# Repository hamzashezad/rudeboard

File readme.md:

# the rudeboard ™

by rudeyboy (rudeyboy#0420 on discord) and hangry -- me (hangry#9198 on discord)

---

introducing the rudeboard:

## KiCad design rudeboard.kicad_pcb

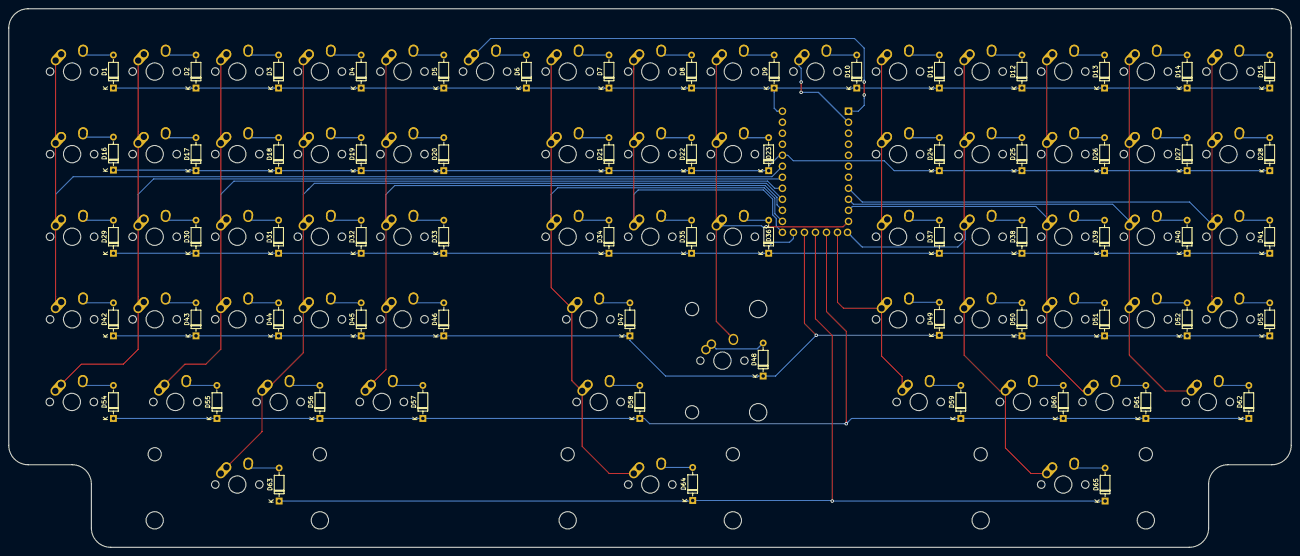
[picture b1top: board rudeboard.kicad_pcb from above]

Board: 2 copper layers, 295.8 x 124.2 mm, 131 parts (1 on the bottom side), 86 nets.

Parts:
D1, D2, D3, D4, D5, D6, D7, D8, D9, D10, D11, D12, D13, D14, D15, D16, D17, D18, D19, D20, D21, D22, D23, D24, D25, D26, D27, D28, D29, D30, D31, D32, D33, D34, D35, D36, D37, D38, D39, D40, D41, D42, D43, D44, D45, D46, D47, D48, D49, D50, D51, D52, D53, D54, D55, D56, D57, D58, D59, D60, D61, D62, D63, D64, D65: D_Small; D_DO-35_SOD27_P7.62mm_Horizontal
MX1, MX2, MX3, MX4, MX5, MX6, MX7, MX8, MX9, MX10, MX11, MX12, MX13, MX14, MX15, MX16, MX17, MX18, MX19, MX20, MX21, MX22, MX23, MX24, MX25, MX26, MX27, MX28, MX29, MX30, MX31, MX32, MX33, MX34, MX35, MX36, MX37, MX38, MX39, MX40, MX41, MX42, MX43, MX44, MX45, MX46, MX49, MX50, MX51, MX52, MX53, MX54, MX56, MX60, MX61: MX-NoLED; MX-1U-NoLED
MX47, MX55, MX57, MX59, MX62: MX-NoLED; MX-1.5U-NoLED
MX48: MX-NoLED; SW_Cherry_MX_ISOEnter_PCB
MX58: MX-NoLED; MX-1.75U-NoLED
MX63, MX64, MX65: MX-NoLED; MX-3U-NoLED
U1: Elite-C

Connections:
/col0: MX1.1, MX16.1, MX29.1, MX42.1, U1.19
/col1: MX2.1, MX17.1, MX30.1, MX43.1, MX54.1, U1.18
/col2: MX3.1, MX18.1, MX31.1, MX44.1, MX55.1, U1.17
/col3: MX4.1, MX19.1, MX32.1, MX45.1, MX56.1, MX63.1, U1.16
/col4: MX5.1, MX20.1, MX33.1, MX46.1, MX57.1, U1.15
/col5: MX6.1, U1.1
/col6: MX7.1, MX21.1, MX34.1, MX47.1, MX58.1, MX64.1, U1.14
/col7: MX8.1, MX22.1, MX35.1, U1.13
/col8: MX9.1, MX23.1, MX36.1, MX48.1, U1.11
/col9: MX10.1, U1.2
/col10: MX11.1, MX24.1, MX37.1, MX49.1, MX59.1, U1.25
/col11: MX12.1, MX25.1, MX38.1, MX50.1, MX60.1, MX65.1, U1.12
/col12: MX13.1, MX26.1, MX39.1, MX51.1, MX61.1, U1.10
/col13: MX14.1, MX27.1, MX40.1, MX52.1, MX62.1, U1.9
/col14: MX15.1, MX28.1, MX41.1, MX53.1, U1.8
/row0: D1.1, D2.1, D3.1, D4.1, D5.1, D6.1, D7.1, D8.1, D9.1, D10.1, D11.1, D12.1, D13.1, D14.1, D15.1, U1.24
/row1: D16.1, D17.1, D18.1, D19.1, D20.1, D21.1, D22.1, D23.1, D24.1, D25.1, D26.1, D27.1, D28.1, U1.20
/row2: D29.1, D30.1, D31.1, D32.1, D33.1, D34.1, D35.1, D36.1, D37.1, D38.1, D39.1, D40.1, D41.1, U1.29
/row3: D42.1, D43.1, D44.1, D45.1, D46.1, D47.1, D48.1, D49.1, D50.1, D51.1, D52.1, D53.1, U1.28
/row4: D54.1, D55.1, D56.1, D57.1, D58.1, D59.1, D60.1, D61.1, D62.1, U1.26
/row5: D63.1, D64.1, D65.1, U1.27
unnamed: D1.2, MX1.2
unnamed: D2.2, MX2.2
unnamed: D3.2, MX3.2
unnamed: D4.2, MX4.2
unnamed: D5.2, MX5.2
unnamed: D6.2, MX6.2
unnamed: D7.2, MX7.2
unnamed: D8.2, MX8.2
unnamed: D9.2, MX9.2
unnamed: D10.2, MX10.2
unnamed: D11.2, MX11.2
unnamed: D12.2, MX12.2
unnamed: D13.2, MX13.2
unnamed: D14.2, MX14.2
unnamed: D15.2, MX15.2
unnamed: D16.2, MX16.2
unnamed: D17.2, MX17.2
unnamed: D18.2, MX18.2
unnamed: D19.2, MX19.2
unnamed: D20.2, MX20.2
unnamed: D21.2, MX21.2
unnamed: D22.2, MX22.2
unnamed: D23.2, MX23.2
unnamed: D24.2, MX24.2
unnamed: D25.2, MX25.2
unnamed: D26.2, MX26.2
unnamed: D27.2, MX27.2
unnamed: D28.2, MX28.2
unnamed: D29.2, MX29.2
unnamed: D30.2, MX30.2
unnamed: D31.2, MX31.2
unnamed: D32.2, MX32.2
unnamed: D33.2, MX33.2
unnamed: D34.2, MX34.2
unnamed: D35.2, MX35.2
unnamed: D36.2, MX36.2
unnamed: D37.2, MX37.2
unnamed: D38.2, MX38.2
unnamed: D39.2, MX39.2
unnamed: D40.2, MX40.2
unnamed: D41.2, MX41.2
unnamed: D42.2, MX42.2
unnamed: D43.2, MX43.2
unnamed: D44.2, MX44.2
unnamed: D45.2, MX45.2
unnamed: D46.2, MX46.2
unnamed: D47.2, MX47.2
unnamed: D48.2, MX48.2
unnamed: D49.2, MX49.2
unnamed: D50.2, MX50.2
unnamed: D51.2, MX51.2
unnamed: D52.2, MX52.2
unnamed: D53.2, MX53.2
unnamed: D54.2, MX54.2
unnamed: D55.2, MX55.2
unnamed: D56.2, MX56.2
unnamed: D57.2, MX57.2
unnamed: D58.2, MX58.2
unnamed: D59.2, MX59.2
unnamed: D60.2, MX60.2
unnamed: D61.2, MX61.2
unnamed: D62.2, MX62.2
unnamed: D63.2, MX63.2
unnamed: D64.2, MX64.2
unnamed: D65.2, MX65.2

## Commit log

2019-06-18 initialization
2019-06-18 add MX switch footprints/schematics
2019-06-18 add gitignore
2019-06-18 proper: add MX footprints/schematics
2019-06-18 add schematic
2019-06-18 finish footprints/routing
2019-06-18 add images
2019-06-18 add gerber files
2019-06-27 update to v1.1
    changes to schematic:
    - potentially better
    - more pins used so more dependant on elite-c but more legible
    routing:
    - looks better than before
    - is more dependant on elite-c (or much less on pro micro)
2019-06-27 add readme
2019-06-30 add project footprint/symbol libraries
2019-06-30 add updated layout images/json
2019-06-30 move images to folder
2019-07-01 prep for reroute
    - delete all existing routes
    - move all diodes to a side of the switch
    - clean elite-c footprint
    - remove front silkscreen
2019-07-02 rerouted pcb
    - better placement of elite-c
    - looks better
2019-07-07 update iso enter to 0deg rotated
2019-07-10 v1.2
    - using traditional matrix -- duplex matrix didn't provide any benifit
    - still dependant on elite-c
    - much better looking pcb
    - everything else is same
2019-07-14 update schamatic to integrate mcu
    - use atmega32u4 as mcu
    - complete schamatics
    - row/cols not final
2019-07-17 route pcb for integrated mcu
    - includes spi pin breakout
2019-08-17 fix silkscreen
    - move dimensions to Dwgs.User
    - move diodes
    - reroute diodes
    - remove unneeded silkscreen/artwork
